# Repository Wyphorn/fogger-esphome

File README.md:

**English** | [Deutsch](README.de.md)

# Fogger with ESPHome

Control a cheap fog machine (labelled **"Fogger 1200W"** on the device, sold as **"LED-1200 Smoke Machine"**, with RGB LEDs) from **Home Assistant**. A **WEMOS D1 Mini** running ESPHome is wired directly into the fogger's controller and talks to Home Assistant over WiFi. The 433 MHz link between remote and fogger is gone.

## How it came about

For Halloween I wanted a ghost to appear at my front door. The motion sensor triggers, the music fades in, the light gets brighter, the strobe kicks in, and then a burst of fog. The fogger only came with a cheap 24-button remote, so I had to get it into Home Assistant somehow.

**Attempt 1: Fingerbots (last year).** My first try was Fingerbots, little push-button robots that physically pressed the buttons on the remote.

**Attempt 2: 433 MHz.** This year I wanted to send the commands directly. The remote works on 433 MHz radio, and with a nanoCUL (CC1101, SIGNALduino) I captured every button. It is simple OOK on 433.92 MHz with an NEC-like code `A7 FC <command> <~command>`. For Halloween the ESP sent the codes through the nanoCUL, and that worked. There were two problems, though:
- Now and then an **OFF arrived as fog ON**. ON and OFF differ in only two bits. As a workaround, the automation sent OFF every 6 s during the fog phase.
- WiFi at the front door is weak. It worked once power saving was off (`power_save_mode: none`).

**Solution: a wire instead of 433 MHz.** After Halloween I opened the fogger. The radio receiver is a separate little board on a 3-pin JST connector labelled **GND / DO / 5V**. DO carries the demodulated signal: HIGH while the remote is transmitting, LOW otherwise. I unplugged the radio module, and now the D1 Mini puts exactly this signal on DO by wire. To the fogger it looks like a remote with perfect reception:
- All 23 buttons work, including colours, strobe and brightness.
- The fogger's heater interlock stays in place.
- No more 433 MHz radio: the D1 Mini reaches the fogger by wire and only uses WiFi to talk to Home Assistant.

One stumbling block was the logic level: the controller does not see the ESP's 3.3 V as HIGH. An NPN transistor as a level shifter pulls DO up to the fogger's 5 V, and with that it worked right away.

## Hardware

| Ref | Part | Value |
|---|---|---|
| U1 | WEMOS D1 Mini (ESP8266) | |
| Q1 | NPN, e.g. S8050 | |
| R1 | Base resistor | 1 kΩ |
| R2 | Pull-up on DO | 10 kΩ |
| C1 | Electrolytic capacitor | 220–470 µF |
| J1 | JST-XH 3-pin to the fogger | |

```
JST 5V  ──┬───────────────── D1 Mini 5V ──┬── C1 +
          │                                │
         R2 10k                            │
          │                                │
JST DO  ──┴── C ┐                          │
                Q1 (NPN)                   │
D1 ── R1 1k ─── B ┤                        │
                │                          │
JST GND ──┬── E ┘                          │
          └───────────────── D1 Mini G  ───┴── C1 −
```

- The D1 Mini is powered from the fogger's 5 V, so it only runs while the fogger is on. The regulator inside the fogger gets warm, but not hot.
- The transistor inverts the signal. That is why the firmware uses `inverted: true`.
- **Don't use D3, D4 or D8.** These are boot pins of the ESP8266, and with the transistor on the base it no longer boots from them.

You'll find the schematic and the PCB (THT, also works on perfboard) in [`kicad/`](kicad/).

## Firmware

[`fogger.yaml`](fogger.yaml) is an ESPHome configuration. Before building it, copy `secrets.example.yaml` to `secrets.yaml` and fill in your details.

In Home Assistant you get:
- **Buttons** for every button on the remote: colours, effects, brightness and light off.
- **Fog burst:** ON, then OFF after an adjustable time. The sequence runs on the ESP, even if Home Assistant drops out in between.
- **Fog ON / OFF:** ON has a safety maximum duration, after which the ESP sends OFF by itself.
- **Diagnostics:** WiFi signal, uptime, reset reason.

The entity names are German (e.g. „Nebelstoß“ = fog burst, „Rot“ = red), because my automations use them. Rename them in `fogger.yaml` as you like.

All codes and the protocol are in [`codes.md`](codes.md).

### Other files
- `fogger_cul.yaml`: the Halloween version, an ESP32-C6 drives a nanoCUL over UART, which transmits.
- `fogger_c6.yaml`: the wired version for an ESP32-C6 instead of a D1 Mini, without the level shifter.
- `rf_log.txt`: the 433 MHz capture log from the nanoCUL.

## ⚠️ Safety

Inside the fog machine there is **mains voltage (230 V)** and a heater block at several hundred degrees. Only open it unplugged. Before connecting anything, check that the low-voltage side is isolated from mains. In my unit a flyback supply with a transformer provides the isolation, and GND to the mains plug pins measured open. Some cheap devices use a capacitive dropper instead, and there GND sits at mains potential.

Build at your own risk.

## License

[MIT](LICENSE)

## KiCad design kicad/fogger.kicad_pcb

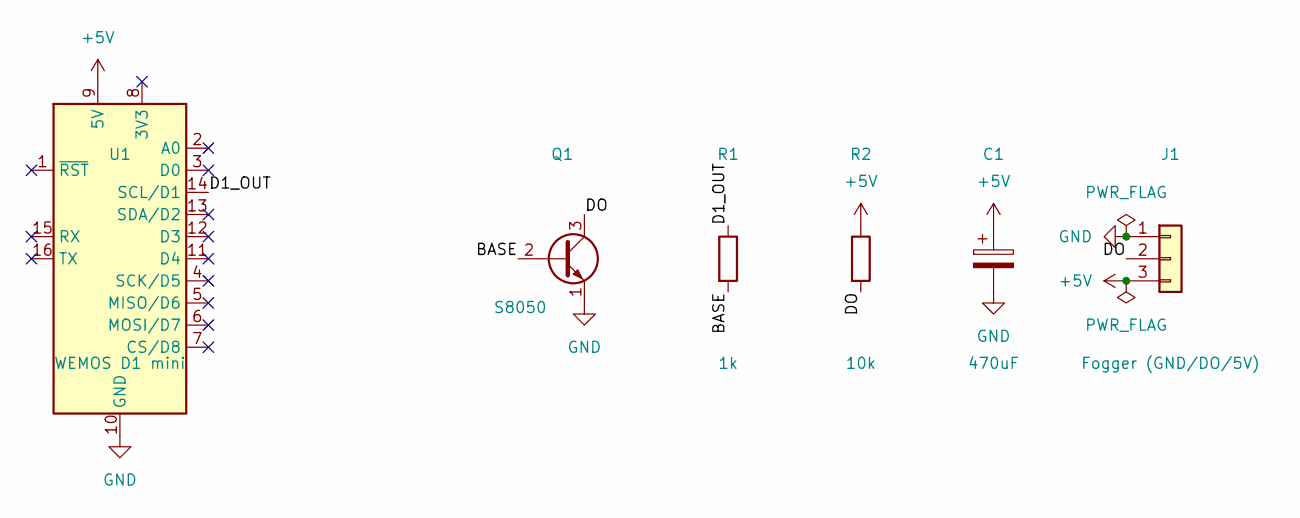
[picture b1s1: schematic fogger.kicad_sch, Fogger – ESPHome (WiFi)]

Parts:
C1: 470uF; CP_Radial_D8.0mm_P3.50mm
J1: Fogger (GND/DO/5V); JST_XH_B3B-XH-A_1x03_P2.50mm_Vertical
Q1: S8050; TO-92_Inline
R1: 1k; R_Axial_DIN0207_L6.3mm_D2.5mm_P7.62mm_Horizontal
R2: 10k; R_Axial_DIN0207_L6.3mm_D2.5mm_P7.62mm_Horizontal
U1: WEMOS D1 mini; WEMOS_D1_mini_light

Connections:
+5V: C1.1, J1.3, R2.1, U1.9 (5V)
/BASE: Q1.2 (B), R1.2
/D1_OUT: R1.1, U1.14 (SCL/D1)
/DO: J1.2, Q1.3 (C), R2.2
GND: C1.2, J1.1, Q1.1 (E), U1.10 (GND)

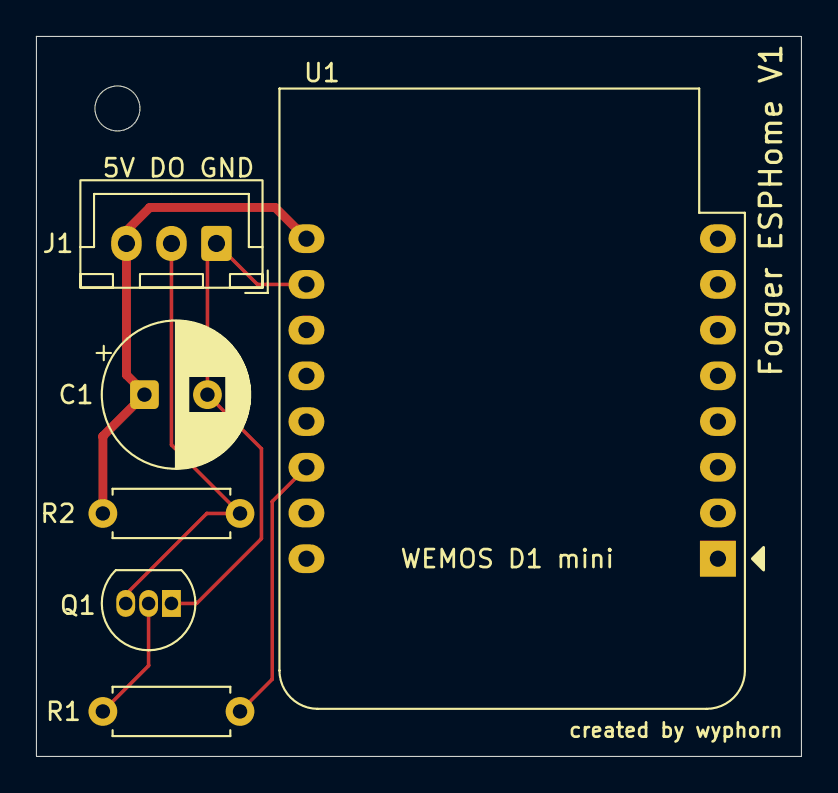
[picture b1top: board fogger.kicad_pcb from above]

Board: 2 copper layers, 42.5 x 40.0 mm, 6 parts (0 on the bottom side), 5 nets.
